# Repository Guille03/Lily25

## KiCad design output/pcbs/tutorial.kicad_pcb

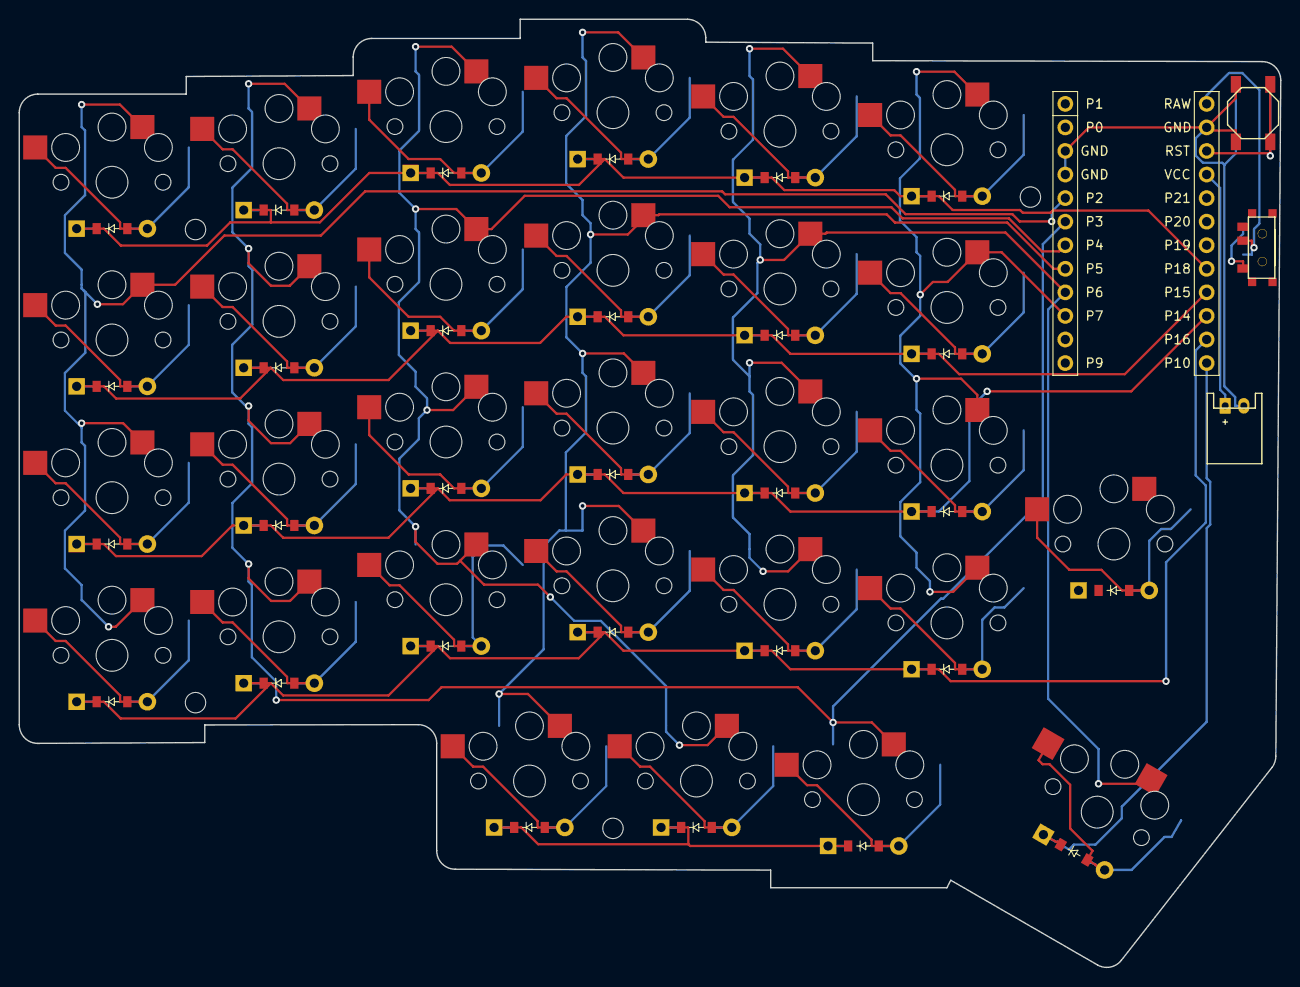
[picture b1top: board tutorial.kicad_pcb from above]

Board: 2 copper layers, 136.0 x 102.2 mm, 66 parts (0 on the bottom side), 45 nets.

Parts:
B1: SW_TACT_ALPS_SKQGABE010
D1, D2, D3, D4, D5, D6, D7, D8, D9, D10, D11, D12, D13, D14, D15, D16, D17, D18, D19, D20, D21, D22, D23, D24, D25, D26, D27, D28, D29: ComboDiode
JST1: JST_PH_S2B-PH-K_02x2.00mm_Angled
MCU1: mcu_nice_nano
MH1, MH2, MH3, MH4: mounting_hole_npth
S1, S2, S3, S4, S5, S6, S7, S8, S9, S10, S11, S12, S13, S14, S15, S16, S17, S18, S19, S20, S21, S22, S23, S24, S25, S26, S27, S28, S29: PG1350
T1: SPDT_C128955

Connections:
D10: D25.1, D26.1, D27.1
GND: B1.1, JST1.2, MCU1.2, MCU1.21, MCU1.22
P2: MCU1.20, S1.1, S2.1, S3.1, S4.1
P3: MCU1.19, S5.1, S6.1, S7.1, S8.1, S27.1
P4: MCU1.18, S9.1, S10.1, S11.1, S12.1, S26.1
P5: MCU1.17, S13.1, S14.1, S15.1, S16.1, S25.1
P6: MCU1.16, S17.1, S18.1, S19.1, S20.1, S29.1
P7: MCU1.15, S21.1, S22.1, S23.1, S24.1
P10: D29.1, MCU1.12
P14: D2.1, D6.1, D10.1, D14.1, D18.1, D22.1, MCU1.10
P15: D3.1, D7.1, D11.1, D15.1, D19.1, D23.1, MCU1.9
P16: D1.1, D5.1, D9.1, D13.1, D17.1, D21.1, MCU1.11
P18: D4.1, D8.1, D12.1, D16.1, D20.1, D24.1, MCU1.8
RAW: MCU1.1, T1.2
RST: B1.2, MCU1.3
VCC: JST1.1, MCU1.4
default_top: D28.2, S28.2
home_unique: D26.2, S26.2
index_bottom: D17.2, S17.2
index_home: D18.2, S18.2
index_num: D20.2, S20.2
index_top: D19.2, S19.2
inner_bottom: D21.2, S21.2
inner_home: D22.2, S22.2
inner_num: D24.2, S24.2
inner_top: D23.2, S23.2
inner_unique: D25.2, S25.2
lefty_bottom: D1.2, S1.2
lefty_home: D2.2, S2.2
lefty_num: D4.2, S4.2
lefty_top: D3.2, S3.2
middle_bottom: D13.2, S13.2
middle_home: D14.2, S14.2
middle_num: D16.2, S16.2
middle_top: D15.2, S15.2
outer_unique: D27.2, S27.2
pinky_bottom: D5.2, S5.2
pinky_home: D6.2, S6.2
pinky_num: D8.2, S8.2
pinky_top: D7.2, S7.2
ring_bottom: D9.2, S9.2
ring_home: D10.2, S10.2
ring_num: D12.2, S12.2
ring_top: D11.2, S11.2
thumb_hey: D29.2, S29.2

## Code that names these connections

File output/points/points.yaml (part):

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        autobind: 10
        skip: false
        asym: both
        colrow: pinky_bottom
        name: main_pinky_bottom
        col_net: P8
        row_net: P3
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        autobind: 10
        skip: false
        asym: both
        colrow: pinky_home
        name: main_pinky_home
        col_net: P8
        row_net: P2
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        autobind: 10
        skip: false
        asym: both
        colrow: pinky_top
        name: main_pinky_top
        col_net: P8
        row_net: P0
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        autobind: 10
        skip: false
        asym: both
        colrow: pinky_num
        name: main_pinky_num
        col_net: P8
        row_net: P1
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
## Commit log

2025-01-23 pcb changes
